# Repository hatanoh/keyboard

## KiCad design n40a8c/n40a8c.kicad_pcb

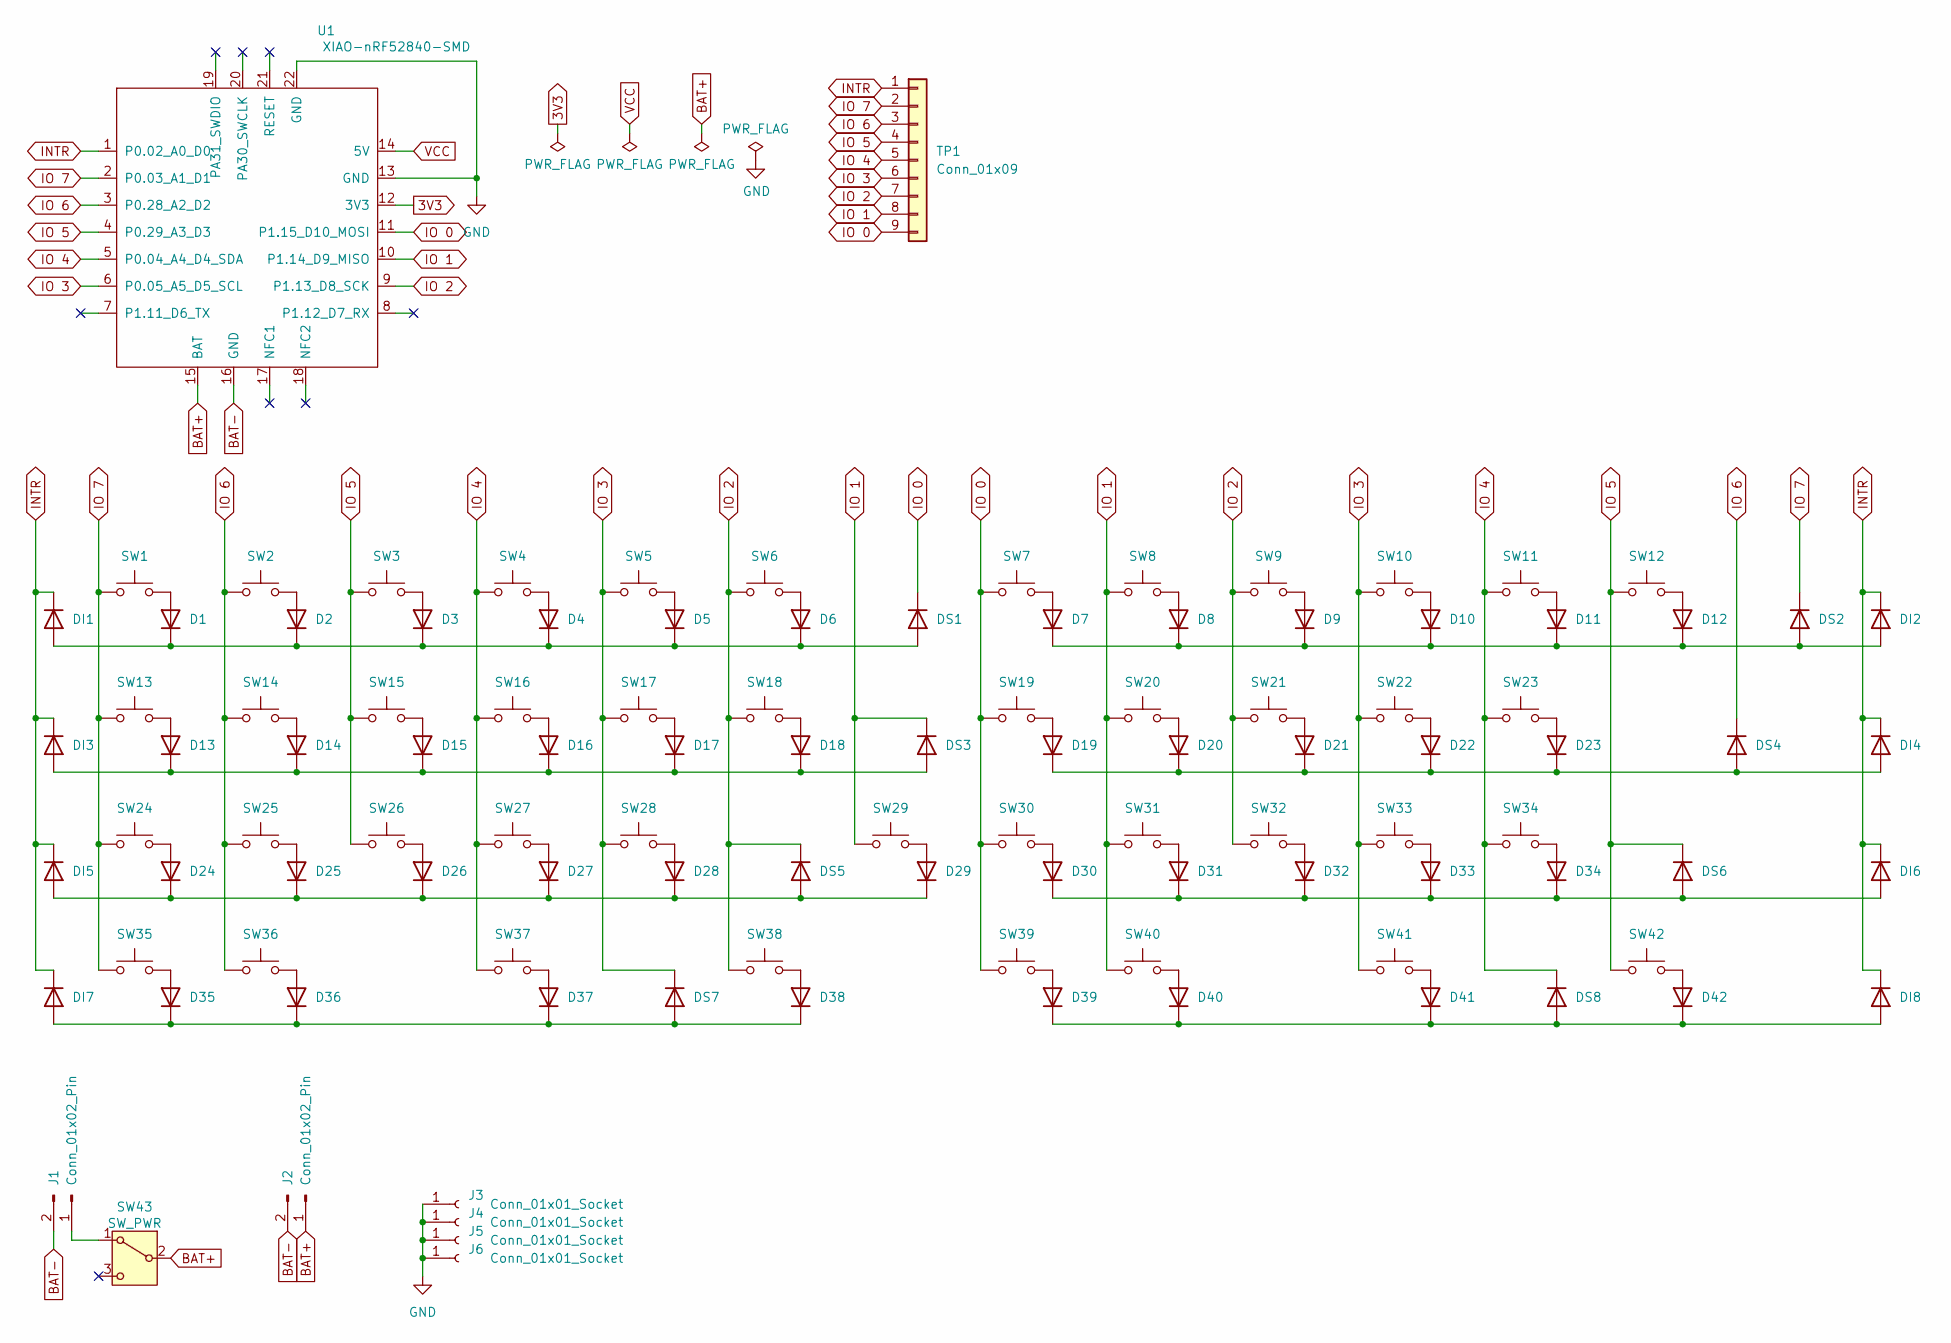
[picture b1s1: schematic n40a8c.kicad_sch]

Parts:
D1, D2, D3, D4, D5, D6, D7, D8, D9, D10, D11, D12, D13, D14, D15, D16, D17, D18, D19, D20, D21, D22, D23, D24, D25, D26, D27, D28, D29, D30, D31, D32, D33, D34, D35, D36, D37, D38, D39, D40, D41, D42: 1N4148W; D_SOD-123
DI1, DI2, DI3, DI4, DI5, DI6, DI7, DI8: 1N4148W; D_SOD-123
DS1, DS2, DS3, DS4, DS5, DS6, DS7, DS8: 1N4148W; D_SOD-123
J1: Conn_01x02_Pin; JST_PH_S2B-PH-K_1x02_P2.00mm_Horizontal
J2: Conn_01x02_Pin; PinHeader_1x02_P2.54mm_Vertical
J3, J4, J5, J6: Conn_01x01_Socket; HOLE_M2
SW1, SW12: SW_Push; CPG151101S11_1.5u
SW2, SW3, SW4, SW5, SW6, SW7, SW8, SW9, SW10, SW11, SW14, SW15, SW16, SW17, SW18, SW19, SW20, SW21, SW22, SW25, SW26, SW27, SW28, SW29, SW30, SW31, SW32, SW33: SW_Push; CPG151101S11_1u
SW13, SW34: SW_Push; CPG151101S11_1.75u
SW23, SW24, SW39: SW_Push; CPG151101S11_2.25u
SW35, SW36, SW37, SW40, SW41, SW42: SW_Push; CPG151101S11_1.25u
SW38: SW_Push; CPG151101S11_2u
SW43: SW_PWR; SLIDE_SWITCH_SK-12D01
TP1: Conn_01x09; PinHeader_1x09_P1.27mm_Conthrough
U1: XIAO-nRF52840-SMD; XIAO-nRF52840-DIP2

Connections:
3V3: U1.12 (3V3)
BAT+: J2.1, SW43.2 (B), U1.15 (BAT)
BAT-: J1.2, J2.2, U1.16 (GND)
GND: J3.1, J4.1, J5.1, J6.1, U1.13 (GND), U1.22 (GND)
INTR: DI1.1 (K), DI2.1 (K), DI3.1 (K), DI4.1 (K), DI5.1 (K), DI6.1 (K), DI7.1 (K), DI8.1 (K), TP1.1, U1.1 (P0.02_A0_D0)
IO 0: DS1.1 (K), SW7.1, SW19.1, SW30.1, SW39.1, TP1.9, U1.11 (P1.15_D10_MOSI)
IO 1: DS3.1 (K), SW8.1, SW20.1, SW29.1, SW31.1, SW40.1, TP1.8, U1.10 (P1.14_D9_MISO)
IO 2: DS5.1 (K), SW6.1, SW9.1, SW18.1, SW21.1, SW32.1, SW38.1, TP1.7, U1.9 (P1.13_D8_SCK)
IO 3: DS7.1 (K), SW5.1, SW10.1, SW17.1, SW22.1, SW28.1, SW33.1, SW41.1, TP1.6, U1.6 (P0.05_A5_D5_SCL)
IO 4: DS8.1 (K), SW4.1, SW11.1, SW16.1, SW23.1, SW27.1, SW34.1, SW37.1, TP1.5, U1.5 (P0.04_A4_D4_SDA)
IO 5: DS6.1 (K), SW3.1, SW12.1, SW15.1, SW26.1, SW42.1, TP1.4, U1.4 (P0.29_A3_D3)
IO 6: DS4.1 (K), SW2.1, SW14.1, SW25.1, SW36.1, TP1.3, U1.3 (P0.28_A2_D2)
IO 7: DS2.1 (K), SW1.1, SW13.1, SW24.1, SW35.1, TP1.2, U1.2 (P0.03_A1_D1)
unnamed: D1.2 (A), SW1.2
unnamed: D1.1 (K), D2.1 (K), D3.1 (K), D4.1 (K), D5.1 (K), D6.1 (K), DI1.2 (A), DS1.2 (A)
unnamed: D2.2 (A), SW2.2
unnamed: D3.2 (A), SW3.2
unnamed: D4.2 (A), SW4.2
unnamed: D5.2 (A), SW5.2
unnamed: D6.2 (A), SW6.2
unnamed: D7.2 (A), SW7.2
unnamed: D8.2 (A), SW8.2
unnamed: D9.2 (A), SW9.2
unnamed: D10.2 (A), SW10.2
unnamed: D7.1 (K), D8.1 (K), D9.1 (K), D10.1 (K), D11.1 (K), D12.1 (K), DI2.2 (A), DS2.2 (A)
unnamed: D11.2 (A), SW11.2
unnamed: D12.2 (A), SW12.2
unnamed: D13.2 (A), SW13.2
unnamed: D13.1 (K), D14.1 (K), D15.1 (K), D16.1 (K), D17.1 (K), D18.1 (K), DI3.2 (A), DS3.2 (A)
unnamed: D14.2 (A), SW14.2
unnamed: D15.2 (A), SW15.2
unnamed: D16.2 (A), SW16.2
unnamed: D17.2 (A), SW17.2
unnamed: D18.2 (A), SW18.2
unnamed: D19.2 (A), SW19.2
unnamed: D19.1 (K), D20.1 (K), D21.1 (K), D22.1 (K), D23.1 (K), DI4.2 (A), DS4.2 (A)
unnamed: D20.2 (A), SW20.2
unnamed: D21.2 (A), SW21.2
unnamed: D22.2 (A), SW22.2
unnamed: D23.2 (A), SW23.2
unnamed: D24.2 (A), SW24.2
unnamed: D24.1 (K), D25.1 (K), D26.1 (K), D27.1 (K), D28.1 (K), D29.1 (K), DI5.2 (A), DS5.2 (A)
unnamed: D25.2 (A), SW25.2
unnamed: D26.2 (A), SW26.2
unnamed: D27.2 (A), SW27.2
unnamed: D28.2 (A), SW28.2
unnamed: D29.2 (A), SW29.2
unnamed: D30.2 (A), SW30.2
unnamed: D30.1 (K), D31.1 (K), D32.1 (K), D33.1 (K), D34.1 (K), DI6.2 (A), DS6.2 (A)
unnamed: D31.2 (A), SW31.2
unnamed: D32.2 (A), SW32.2
unnamed: D33.2 (A), SW33.2
unnamed: D34.2 (A), SW34.2
unnamed: D35.2 (A), SW35.2
unnamed: D35.1 (K), D36.1 (K), D37.1 (K), D38.1 (K), DI7.2 (A), DS7.2 (A)
unnamed: D36.2 (A), SW36.2
unnamed: D37.2 (A), SW37.2
unnamed: D38.2 (A), SW38.2
unnamed: D39.2 (A), SW39.2
unnamed: D39.1 (K), D40.1 (K), D41.1 (K), D42.1 (K), DI8.2 (A), DS8.2 (A)
unnamed: D40.2 (A), SW40.2
unnamed: D41.2 (A), SW41.2
unnamed: D42.2 (A), SW42.2
unnamed: J1.1, SW43.1 (A)
VCC: U1.14 (5V)

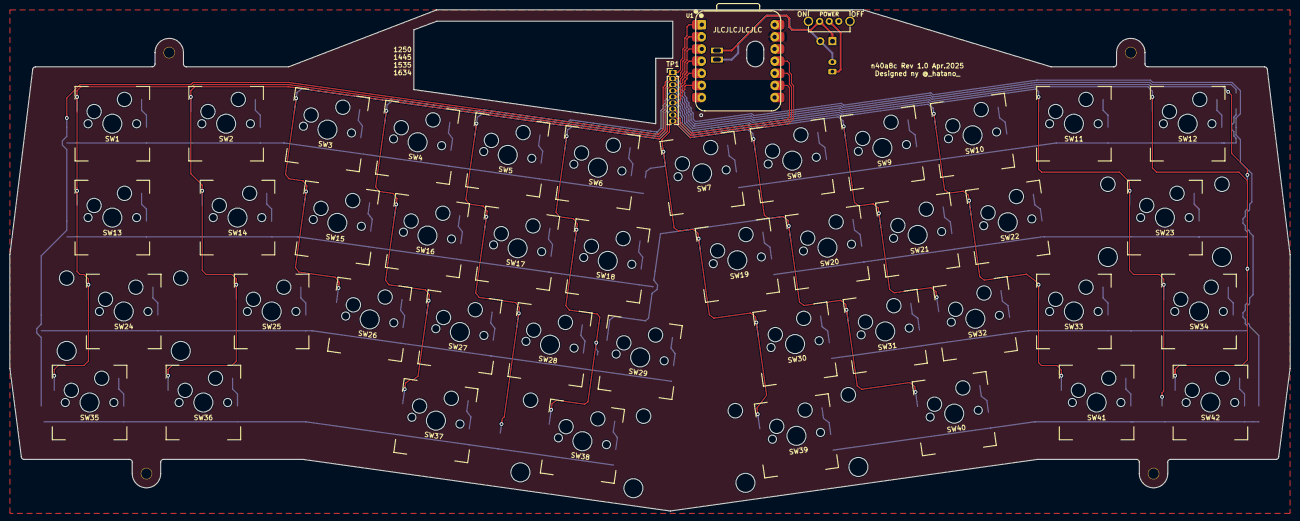
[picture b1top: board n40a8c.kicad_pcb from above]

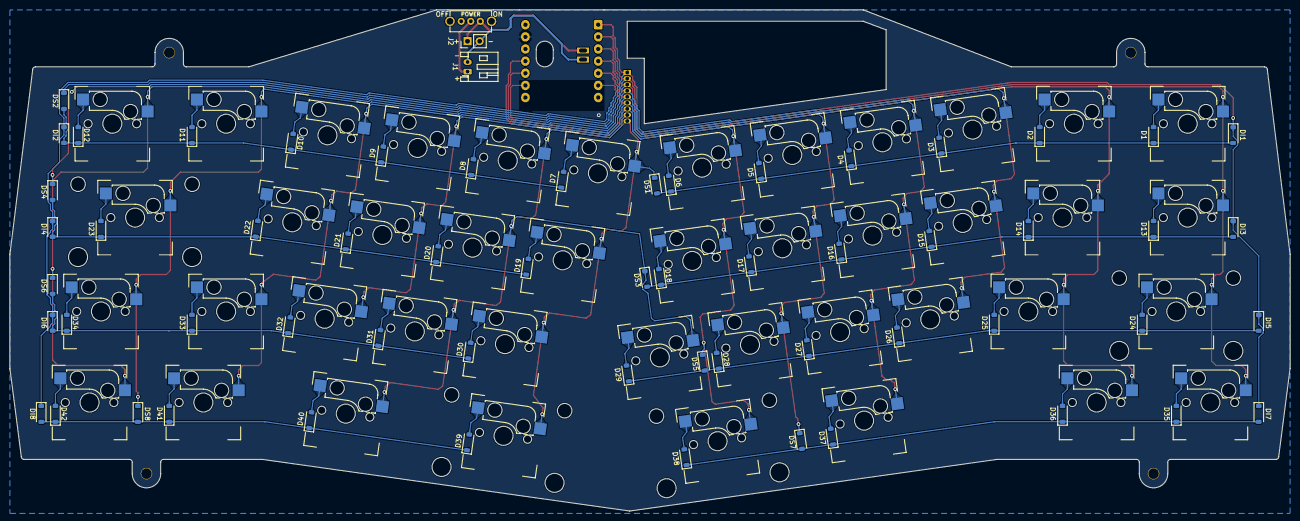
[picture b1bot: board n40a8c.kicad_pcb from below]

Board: 2 copper layers, 267.9 x 104.9 mm, 109 parts (103 on the bottom side), 63 nets.

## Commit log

2025-03-28 add new keyboard n40a8
2025-03-28 move Diode
2025-03-30 wired
2025-03-31 wiring complete
2025-03-31 revise wiring
2025-04-01 revise footprint
2025-04-01 revise footprint for PCBA
2025-04-01 revise foot print for PCBA
2025-04-06 revice for PCBA
2025-04-06 modified footprint
2025-04-06 add pos file
2025-04-07 modified wiring
2025-04-10 add Charlieplex wiring
2025-04-10 modify
2025-04-11 use SMD
2025-04-11 rewire
2025-04-19 change pin assign.
